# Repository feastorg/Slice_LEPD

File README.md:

# Photometer Slice

Photometer using LED and photodiode slice for BREAD.

## Introduction

[Short introduction on the project.]

## Usage

[Explain how to use the project. Include examples and screenshots if applicable.]

## Documentation

Please refer to the [docs](/docs) for more info.

---

<div align="center">
  
</div>

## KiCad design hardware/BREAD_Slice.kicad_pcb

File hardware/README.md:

# LED-Photodiode Optical Density Meter

## Parts

- LEDs
  - PD: SFH 213 FA
  - IR: INL-5AMIR15
  - from: https://forum.pioreactor.com/t/od600-or-900-what-is-the-part-number-for-the-ir-led-and-photodiode/375

## Subcomponents

1. **PWM-to-DAC Filter (Lower Left)**

   - **Input:** A PWM signal enters through an RC network (two resistors and two capacitors) that smooths it into a DC “DAC” voltage.
   - **Outputs:** This DAC voltage is fed to:
     - The noninverting (+) input of the LM339 comparator (top amplifier).
     - The noninverting (+) input of the MCP6242 op amp (bottom amplifier).

2. **LM339 Comparator (Top)**

   - **+ Input:** Receives the filtered DAC voltage.
   - **− Input:** Receives a reference or filtered voltage derived from the +5 V rail.
   - **Output:**
     - Uses an open-collector configuration with a pull-up resistor (1 kΩ) to the +5 V rail.
     - A 200 kΩ resistor from the output back to the DAC input provides hysteresis.
     - The comparator output drives the base of the BC858 PNP transistor through a 10 kΩ resistor.

3. **BC858 PNP Transistor (Top Switch)**

   - **Collector:** Connected directly to the +5 V rail.
   - **Base:** Driven by the LM339 comparator output (via a 10 kΩ resistor).
   - **Emitter:** Connected to the common output node, which is shared with:
     - The drain of the BSS806 N-channel MOSFET.
     - The cathode of the LED (which is further protected by a TVS diode).

4. **MCP6242 Op Amp (Bottom)**

   - **+ Input:** Receives the same DAC voltage from the PWM filter.
   - **− Input:** Connected to the source of the BSS806 MOSFET (the voltage sensed across a 10 Ω resistor).
   - **Output:** Drives the gate of the BSS806 MOSFET (labeled “FET_GATE”) to regulate current.

5. **BSS806 N-Channel MOSFET (Bottom Switch)**

   - **Drain:** Tied to the common output node (also the emitter of the BC858).
   - **Source:** Connects to a 10 Ω resistor that goes to ground. This resistor acts as a current-sense element.
   - **Function:** Controlled by the op amp to regulate the voltage at the source, and hence the current through the LED.

6. **LED and 10 Ω Sense Resistor**

   - **LED Anode:** Connected to the +5 V rail.
   - **LED Cathode:** Connected to the common node (junction of BC858 emitter and MOSFET drain).
   - **Current Path:** +5 V → LED → common node → MOSFET → 10 Ω resistor → Ground.
   - **Sensing:** The voltage across the 10 Ω resistor is used by the op amp for current regulation.

7. **TVS Diode (DF2S6.8M)**
   - **Connection:** Placed between the common output node and ground.
   - **Function:** Provides transient and ESD protection to the circuit.

---

## 2) Overall Function and How It Works

1. **PWM Filtering to Create a DAC:**  
   A low-pass RC filter converts a PWM signal into a stable DC voltage. This voltage represents the desired setpoint for the LED current or voltage.

2. **Op Amp and MOSFET Current Regulation:**

   - The MCP6242 op amp compares the DAC setpoint with the voltage at the MOSFET source (across the 10 Ω sense resistor).
   - Based on this comparison, the op amp adjusts the gate voltage of the BSS806 MOSFET.
   - This regulation maintains the correct current through the LED by ensuring that the sensed voltage (proportional to current) matches the DAC setpoint.

3. **Comparator and PNP Transistor Threshold Control:**

   - The LM339 comparator monitors the DAC voltage against a reference (from the +5 V supply).
   - Through its open-collector output (with hysteresis via the 200 kΩ resistor), it determines if the operating condition is within the desired range.
   - The comparator’s output drives the BC858 PNP transistor, which can provide an alternate current path or act as a switch to either enable or limit the LED current based on threshold conditions.

4. **Combined Regulation and Protection:**
   - **Current Flow:** The LED current flows from the +5 V rail through the LED, into the common node, through the MOSFET, and finally through the 10 Ω resistor to ground.
   - **Protection:** A TVS diode is connected at the output node to guard against voltage spikes.
   - **Feedback:** The op amp continuously adjusts the MOSFET’s gate voltage to ensure that the voltage across the 10 Ω resistor (and thus the LED current) matches the desired value set by the DAC voltage.

**In summary:**  
The circuit converts a PWM signal to a DC level that serves as a setpoint for LED current. The op amp and MOSFET form a linear regulator that adjusts the LED current, while the comparator and PNP transistor provide threshold-based switching or clamping for additional control and protection.

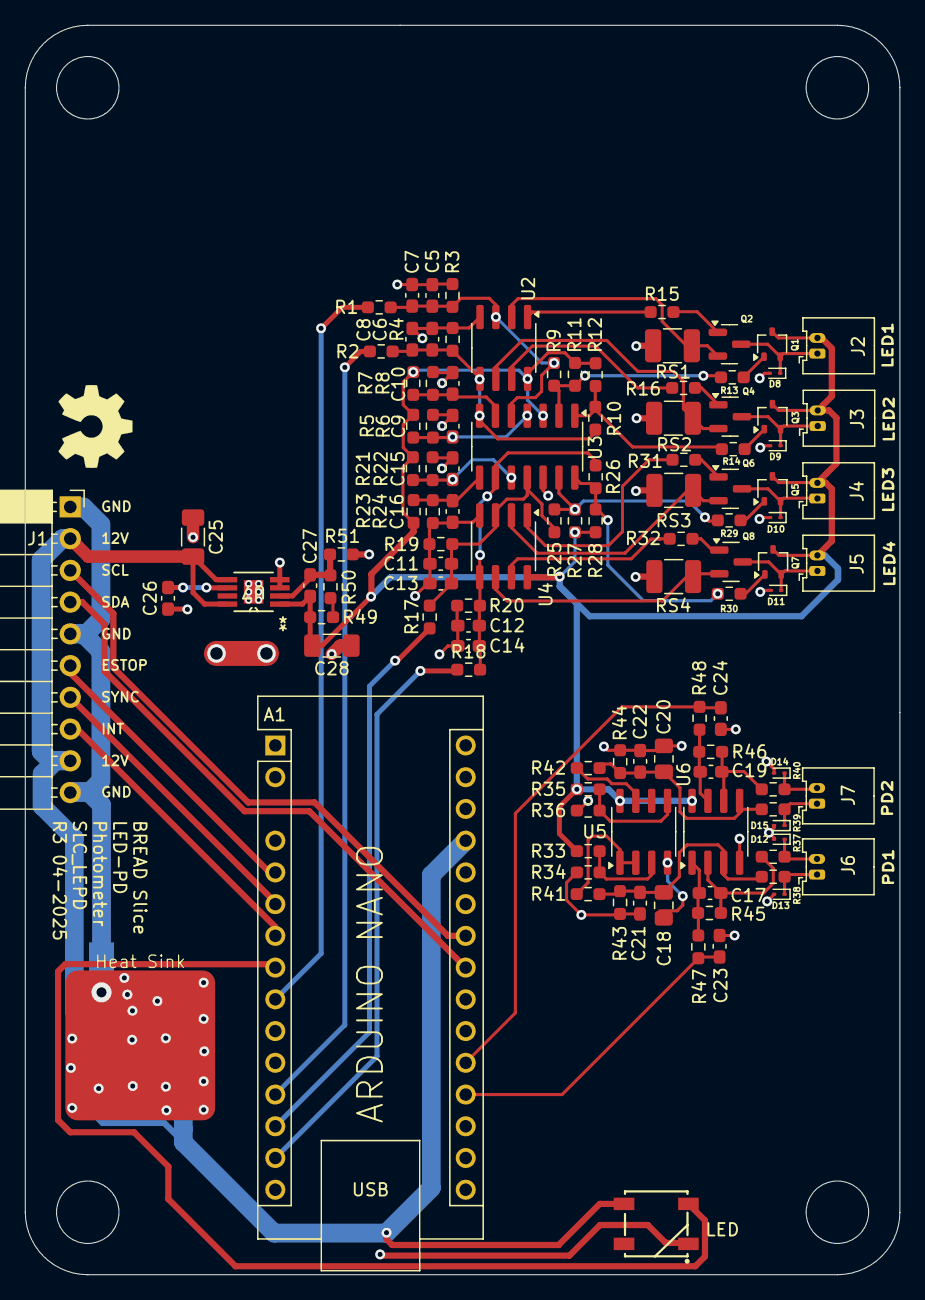
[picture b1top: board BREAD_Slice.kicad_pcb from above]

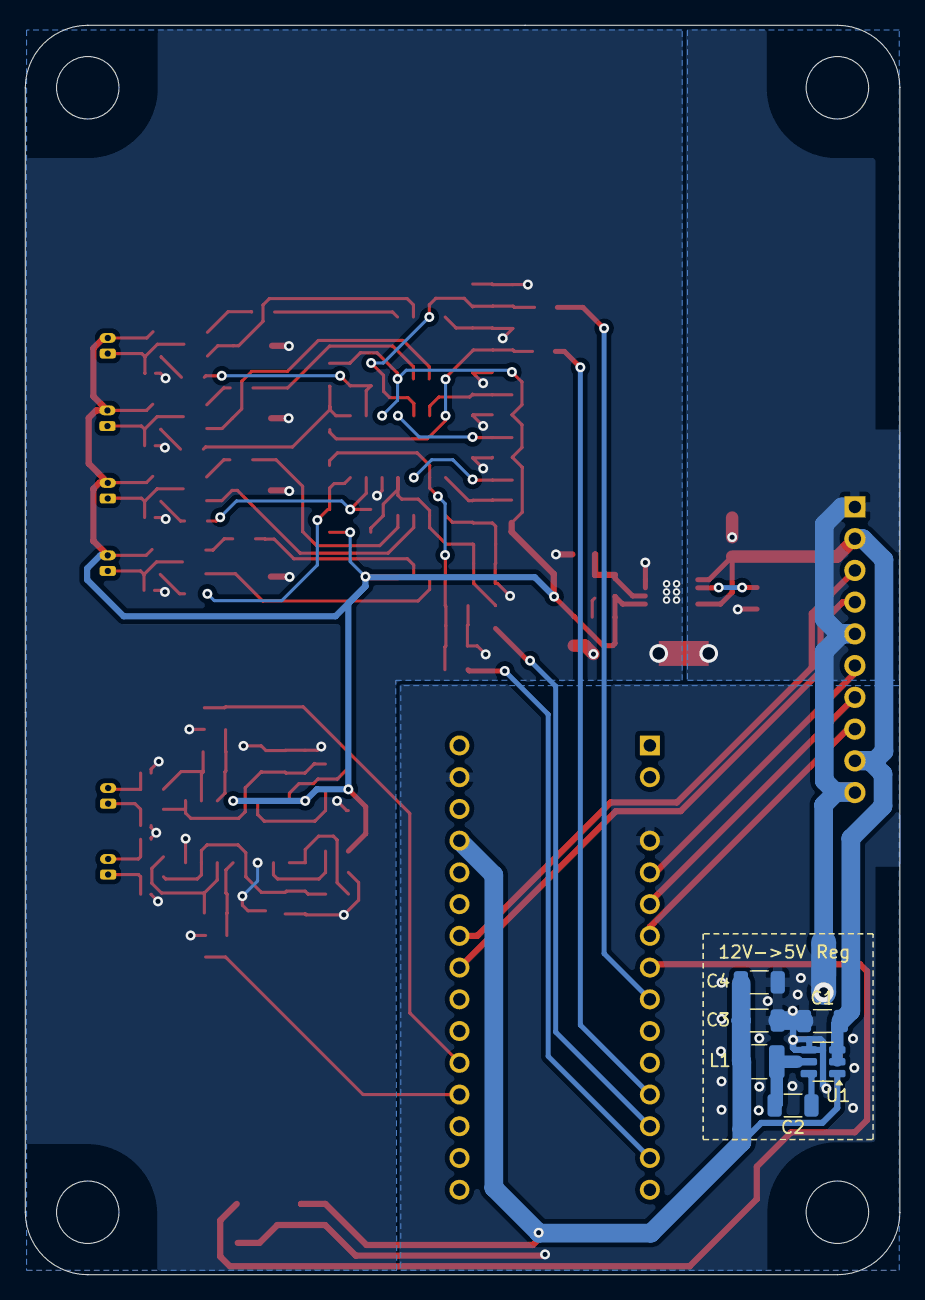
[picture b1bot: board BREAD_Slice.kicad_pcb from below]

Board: 2 copper layers, 70.0 x 100.0 mm, 124 parts (7 on the bottom side), 69 nets.

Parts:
A1: Arduino_Nano_v3.x; Arduino_Nano
C1, C3, C4: 22uF; C_1206_3216Metric
C2: 100nF; C_1206_3216Metric
C5, C6, C11, C12: 1u; C_0603_1608Metric_Pad1.08x0.95mm_HandSolder
C7, C8, C13, C14: 0.22u; C_0603_1608Metric_Pad1.08x0.95mm_HandSolder
C9, C10, C15, C16, C17, C19: 10n; C_0603_1608Metric_Pad1.08x0.95mm_HandSolder
C18, C20: 10u; C_0805_2012Metric_Pad1.18x1.45mm_HandSolder
C21, C22, C23, C24: 0.1u; C_0603_1608Metric_Pad1.08x0.95mm_HandSolder
C25, C28: 10u X7R; C_1206_3216Metric_Pad1.33x1.80mm_HandSolder
C26, C27: 10n X7R; C_0603_1608Metric_Pad1.08x0.95mm_HandSolder
D1: WS2812B_5050; WS2812-5050-4PIN
D8, D9, D10, D11, D12, D13, D14, D15: DF2S6.8MFS_L3M; D_SOD-923
H1, H2, H3, H4: MountingHole; MountingHole_5mm
HS1: Heatsink_Pad; Thermal_Pad
J1: Conn_01x10_Female; PinSocket_1x10_P2.54mm_Horizontal
J2, J3, J4, J5, J6, J7: Conn_01x02; Molex_PicoBlade_53048-0210_1x02_P1.25mm_Horizontal
L1: 4.7uH; L_1210_3225Metric
Logo1: Logo_Open_Hardware_Small; OSHW-Symbol_6.7x6mm_SilkScreen
NT1, NT2: NetTie_2; NetTie-2_SMD_Pad2.0mm
Q1, Q3, Q5, Q7: BC858BWT1G; SOT-323_SC-70
Q2, Q4, Q6, Q8: BSS806NH6327XTSA1; SOT-23
R1, R2, R17, R18: 3.3k 1%; R_0603_1608Metric_Pad0.98x0.95mm_HandSolder
R3, R4, R19, R20: 1.6k 1%; R_0603_1608Metric_Pad0.98x0.95mm_HandSolder
R5, R7, R21, R23: 64.9k 1%; R_0603_1608Metric_Pad0.98x0.95mm_HandSolder
R6, R8, R22, R24: 430 1%; R_0603_1608Metric_Pad0.98x0.95mm_HandSolder
R9, R10, R25, R26: 200k 1%; R_0603_1608Metric_Pad0.98x0.95mm_HandSolder
R11, R12, R27, R28, R41, R42: 1k 1%; R_0603_1608Metric_Pad0.98x0.95mm_HandSolder
R13, R14, R15, R16, R29, R30, R31, R32, R47, R48: 10k 1%; R_0603_1608Metric_Pad0.98x0.95mm_HandSolder
R33, R35: 10k; R_0603_1608Metric_Pad0.98x0.95mm_HandSolder
R34, R36: 20k; R_0603_1608Metric_Pad0.98x0.95mm_HandSolder
R37, R38, R39, R40: 0R; R_0603_1608Metric_Pad0.98x0.95mm_HandSolder
R43, R44: 15 1%; R_0603_1608Metric_Pad0.98x0.95mm_HandSolder
R45, R46: 1.5M 1%; R_0603_1608Metric_Pad0.98x0.95mm_HandSolder
R49: 300k 1%; R_0603_1608Metric_Pad0.98x0.95mm_HandSolder
R50: 71.5k 1%; R_0603_1608Metric_Pad0.98x0.95mm_HandSolder
R51: 100k 1%; R_0603_1608Metric_Pad0.98x0.95mm_HandSolder
RS1, RS2, RS3, RS4: 10 0.5W 1%; R_1210_3225Metric_Pad1.30x2.65mm_HandSolder
U1: AP63205; TSOT-23-6
U2, U4, U5: MCP6242T-E/SN; SOIC-8_3.9x4.9mm_P1.27mm
U3: LM339B; SOIC-14_3.9x8.7mm_P1.27mm
U6: TLV9142; SOIC-8_3.9x4.9mm_P1.27mm
U7: TPS7A4901DGNR; DGN8_1P89X1P57

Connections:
+5V: A1.27 (+5V), C3.2, C4.2, D1.1 (VDD), L1.2, U1.1 (FB)
+5VA: C27.2, C28.2, J2.2, J3.2, J4.2, J5.2, Q1.3 (C), Q3.3 (C), Q5.3 (C), Q7.3 (C), R5.2, R7.2, R11.1, R12.1, R21.2, R23.2, R27.1, R28.1, R33.1, R35.1, R49.2, U2.8 (V+), U3.3 (V+), U4.8 (V+), U5.8 (V+), U6.8 (V+), U7.1 (OUT)
+12V: C1.2, C25.2, J1.2, J1.9, U1.2 (EN), U1.3 (VIN), U7.5 (EN), U7.8 (IN)
/ESTOP: A1.5 (D2), J1.6
/I2C_CLK: A1.24 (A5), J1.3
/I2C_DAT: A1.23 (A4), J1.4
/INT: A1.6 (D3), J1.7
/LED: A1.8 (D5), D1.4 (DIN)
/Linear Constant‐Current LED Driver x4/COMP_OUT_1: R9.2, R11.2, R13.1, U3.2
/Linear Constant‐Current LED Driver x4/COMP_OUT_2: R10.2, R12.2, R14.1, U3.1
/Linear Constant‐Current LED Driver x4/COMP_OUT_3: R25.2, R27.2, R29.1, U3.13
/Linear Constant‐Current LED Driver x4/COMP_OUT_4: R26.2, R28.2, R30.1, U3.14
/Linear Constant‐Current LED Driver x4/COMP_REF_1: C9.1, R5.1, R6.1, U3.4 (-)
/Linear Constant‐Current LED Driver x4/COMP_REF_2: C10.1, R7.1, R8.1, U3.6 (-)
/Linear Constant‐Current LED Driver x4/COMP_REF_3: C15.1, R21.1, R22.1, U3.10 (-)
/Linear Constant‐Current LED Driver x4/COMP_REF_4: C16.1, R23.1, R24.1, U3.8 (-)
/Linear Constant‐Current LED Driver x4/DAC_1: C5.1, C7.1, R1.2, R3.1, R9.1, U2.3 (+), U3.5 (+)
/Linear Constant‐Current LED Driver x4/DAC_2: C6.1, C8.1, R2.2, R4.1, R10.1, U2.5 (+), U3.7 (+)
/Linear Constant‐Current LED Driver x4/DAC_3: C11.1, C13.1, R17.2, R19.1, R25.1, U3.11 (+), U4.3 (+)
/Linear Constant‐Current LED Driver x4/DAC_4: C12.1, C14.1, R18.2, R20.1, R26.1, U3.9 (+), U4.5 (+)
/Linear Constant‐Current LED Driver x4/FEEDBACK_1: Q2.2 (S), RS1.1, U2.2 (-)
/Linear Constant‐Current LED Driver x4/FEEDBACK_2: Q4.2 (S), RS2.1, U2.6 (-)
/Linear Constant‐Current LED Driver x4/FEEDBACK_3: Q6.2 (S), RS3.1, U4.2 (-)
/Linear Constant‐Current LED Driver x4/FEEDBACK_4: Q8.2 (S), RS4.1, U4.6 (-)
/Linear Constant‐Current LED Driver x4/LED_CATHODE_1: D8.1, J2.1, Q1.2 (E), Q2.3 (D)
/Linear Constant‐Current LED Driver x4/LED_CATHODE_2: D9.1, J3.1, Q3.2 (E), Q4.3 (D)
/Linear Constant‐Current LED Driver x4/LED_CATHODE_3: D10.1, J4.1, Q5.2 (E), Q6.3 (D)
/Linear Constant‐Current LED Driver x4/LED_CATHODE_4: D11.1, J5.1, Q7.2 (E), Q8.3 (D)
/Linear Constant‐Current LED Driver x4/NFET_GATE_1: Q2.1 (G), R15.2
/Linear Constant‐Current LED Driver x4/NFET_GATE_2: Q4.1 (G), R16.2
/Linear Constant‐Current LED Driver x4/NFET_GATE_3: Q6.1 (G), R31.2
/Linear Constant‐Current LED Driver x4/NFET_GATE_4: Q8.1 (G), R32.2
/Linear Constant‐Current LED Driver x4/OPAMP_OUT_1: R15.1, U2.1
/Linear Constant‐Current LED Driver x4/OPAMP_OUT_2: R16.1, U2.7
/Linear Constant‐Current LED Driver x4/OPAMP_OUT_3: R31.1, U4.1
/Linear Constant‐Current LED Driver x4/OPAMP_OUT_4: R32.1, U4.7
/Linear Constant‐Current LED Driver x4/PNPBJT_BASE_1: Q1.1 (B), R13.2
/Linear Constant‐Current LED Driver x4/PNPBJT_BASE_2: Q3.1 (B), R14.2
/Linear Constant‐Current LED Driver x4/PNPBJT_BASE_3: Q5.1 (B), R29.2
/Linear Constant‐Current LED Driver x4/PNPBJT_BASE_4: Q7.1 (B), R30.2
/PD1: A1.19 (A0), C23.1, R47.2
/PD2: A1.20 (A1), C24.1, R48.2
/PWM1: A1.9 (D6), R1.1
/PWM2: A1.12 (D9), R2.1
/PWM3: A1.13 (D10), R17.1
/PWM4: A1.14 (D11), R18.1
/Photodiode TIA Amplifier x2/3V3_2: R42.1, U5.6 (-), U5.7
/Photodiode TIA Amplifier x2/+3V3_1: R41.1, U5.1, U5.2 (-)
/Photodiode TIA Amplifier x2/PD_ANODE1: D12.1, J6.2, R37.1
/Photodiode TIA Amplifier x2/PD_ANODE2: D14.1, J7.2, R39.1
/Photodiode TIA Amplifier x2/PD_CATHODE1: D13.1, J6.1, R38.1
/Photodiode TIA Amplifier x2/PD_CATHODE2: D15.1, J7.1, R40.1
/Photodiode TIA Amplifier x2/TIA_BIAS_1: C18.1, C21.1, R38.2, R41.2, R43.1, U6.3 (+)
/Photodiode TIA Amplifier x2/TIA_BIAS_2: C20.1, C22.1, R40.2, R42.2, R44.1, U6.5 (+)
/Photodiode TIA Amplifier x2/TIA_FEEDBACK_1: C17.1, R37.2, R45.1, U6.2 (-)
/Photodiode TIA Amplifier x2/TIA_FEEDBACK_2: C19.1, R39.2, R46.1, U6.6 (-)
/Photodiode TIA Amplifier x2/TIA_OUT_1: C17.2, R45.2, R47.1, U6.1
/Photodiode TIA Amplifier x2/TIA_OUT_2: C19.2, R46.2, R48.1, U6.7
/SYNC: A1.7 (D4), J1.8
GND: A1.4 (GND), A1.29 (GND), C1.1, C3.1, C4.1, D1.3 (VSS), HS1.1, NT1.1, U1.4 (GND)
GNDA: C5.2, C6.2, C7.2, C8.2, C9.2, C10.2, C11.2, C12.2, C13.2, C14.2, C15.2, C16.2, C18.2, C20.2, C21.2, C22.2, C23.2, C24.2, C28.1, D8.2, D9.2, D10.2, D11.2, D12.2, D13.2, D14.2, D15.2, NT2.2, R3.2, R4.2, R6.2, R8.2, R19.2, R20.2, R22.2, R24.2, R34.2, R36.2, R43.2, R44.2, R51.1, RS1.2, RS2.2, RS3.2, RS4.2, U2.4 (V-), U3.12 (V-), U4.4 (V-), U5.4 (V-), U6.4 (V-), U7.3 (NC), U7.4 (GND), U7.EPAD
GNDPWR: C25.1, C26.1, J1.1, J1.5, J1.10, NT1.2, NT2.1
unnamed: R49.1, R50.2
unnamed: C2.2, U1.6 (BST)
unnamed: C2.1, L1.1, U1.5 (SW)
unnamed: R33.2, R34.1, U5.3 (+)
unnamed: R35.2, R36.1, U5.5 (+)
unnamed: C27.1, R50.1, R51.2, U7.2 (FB)
unnamed: C26.2, U7.6 (NR/SS)

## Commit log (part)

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2024-09-10 set repo
2025-04-05 added opamps
2025-04-06 completed CC driver for LEDs
2025-04-12 finalized initial schematic and board
2025-04-19 minor tweaks
2026-05-20 Add slice.yaml manifest (schema v1.0)
2026-05-24 Add KiBot/docs pipeline
2026-05-24 Update TODO with CI findings
2026-05-24 Standardize TODO.md with Pass 1/Pass 2 structure
